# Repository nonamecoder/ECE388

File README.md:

# ECE388
GitHub repository for ECE388 project. Place all project files here.

## Project Description
RFID Automated boom barrier <br/>
### Specifications

###### Inputs <br/>
- Raspberry Pi Pico W(Wireless)
- MRFC522 RFID Reader
  - Detects Mifare 1K Classic Cards based on UID
    - UID ( Unique Identifier)

###### Outputs <br/>

- LCD 
  - Indicate either access granted or access denied.
- Buzzer
  - Access granted buzzer sound1
  - Access denied buzzer sound2
  - Master key buzzer sound for demo!
 - Servo
  - Rotate servo if access is granted
  - Do nothing if access is denied.
  
  ###### Next Steps <br/>
  Following can be achieved using IFTTT, guide can be found [here](https://www.tomshardware.com/how-to/connect-raspberry-pi-pico-w-to-twitter-via-ifttt).
  - If access granted
    - Send notification
  - If access denied
    - Send notification

## References <br/>
- [RFID](https://microcontrollerslab.com/raspberry-pi-pico-rfid-rc522-micropython/)

- [Servo](https://microcontrollerslab.com/servo-motor-raspberry-pi-pico-micropython/)

- [LCD](https://www.tomshardware.com/how-to/lcd-display-raspberry-pi-pico)

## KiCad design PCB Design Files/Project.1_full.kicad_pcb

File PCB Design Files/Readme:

The PCB Design files are added to this folder.

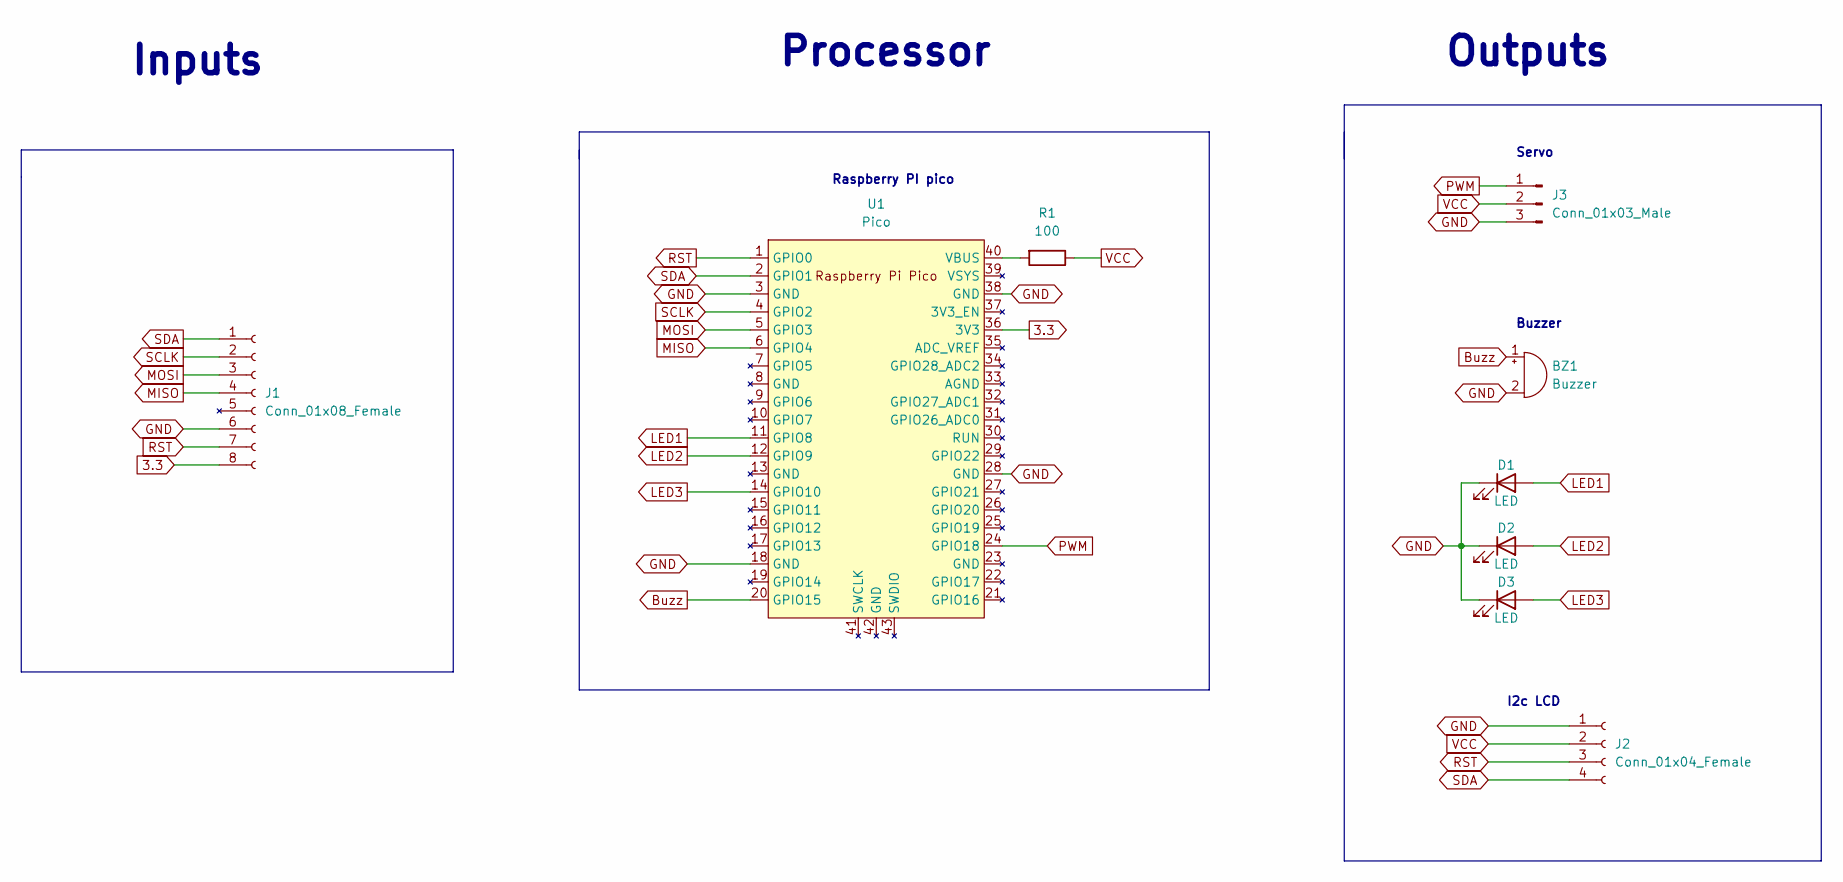
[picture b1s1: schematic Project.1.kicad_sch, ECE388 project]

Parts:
BZ1: Buzzer; Buzzer_12x9.5RM7.6
D1, D2, D3: LED; LED_D5.0mm
J1: Conn_01x08_Female; PinSocket_1x08_P2.54mm_Vertical
J2: Conn_01x04_Female; PinSocket_1x04_P2.54mm_Vertical
J3: Conn_01x03_Male; PinHeader_1x03_P2.54mm_Vertical
R1: 100; R_Axial_DIN0309_L9.0mm_D3.2mm_P12.70mm_Horizontal
U1: Pico; PicoPCB

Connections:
3.3: J1.8 (3.3V), U1.36 (3V3)
Buzz: BZ1.1 (-), U1.20 (GPIO15)
GND: BZ1.2 (+), D1.1 (K), D2.1 (K), D3.1 (K), J1.6 (GND), J2.1 (GND), J3.3, U1.3 (GND), U1.18 (GND), U1.28 (GND), U1.38 (GND)
LED1: D1.2 (A), U1.11 (GPIO8)
LED2: D2.2 (A), U1.12 (GPIO9)
LED3: D3.2 (A), U1.14 (GPIO10)
MISO: J1.4 (MISO), U1.6 (GPIO4)
MOSI: J1.3 (MOSI), U1.5 (GPIO3)
unnamed: R1.2, U1.40 (VBUS)
PWM: J3.1, U1.24 (GPIO18)
RST: J1.7 (RST), J2.3 (SDA), U1.1 (GPIO0)
SCLK: J1.2 (SCK), U1.4 (GPIO2)
SDA: J1.1 (SDA), J2.4 (SCL), U1.2 (GPIO1)
VCC: J2.2 (VCC), J3.2, R1.1

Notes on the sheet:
Buzzer
Processor
Outputs
I2c LCD
Inputs
Servo
Raspberry PI pico

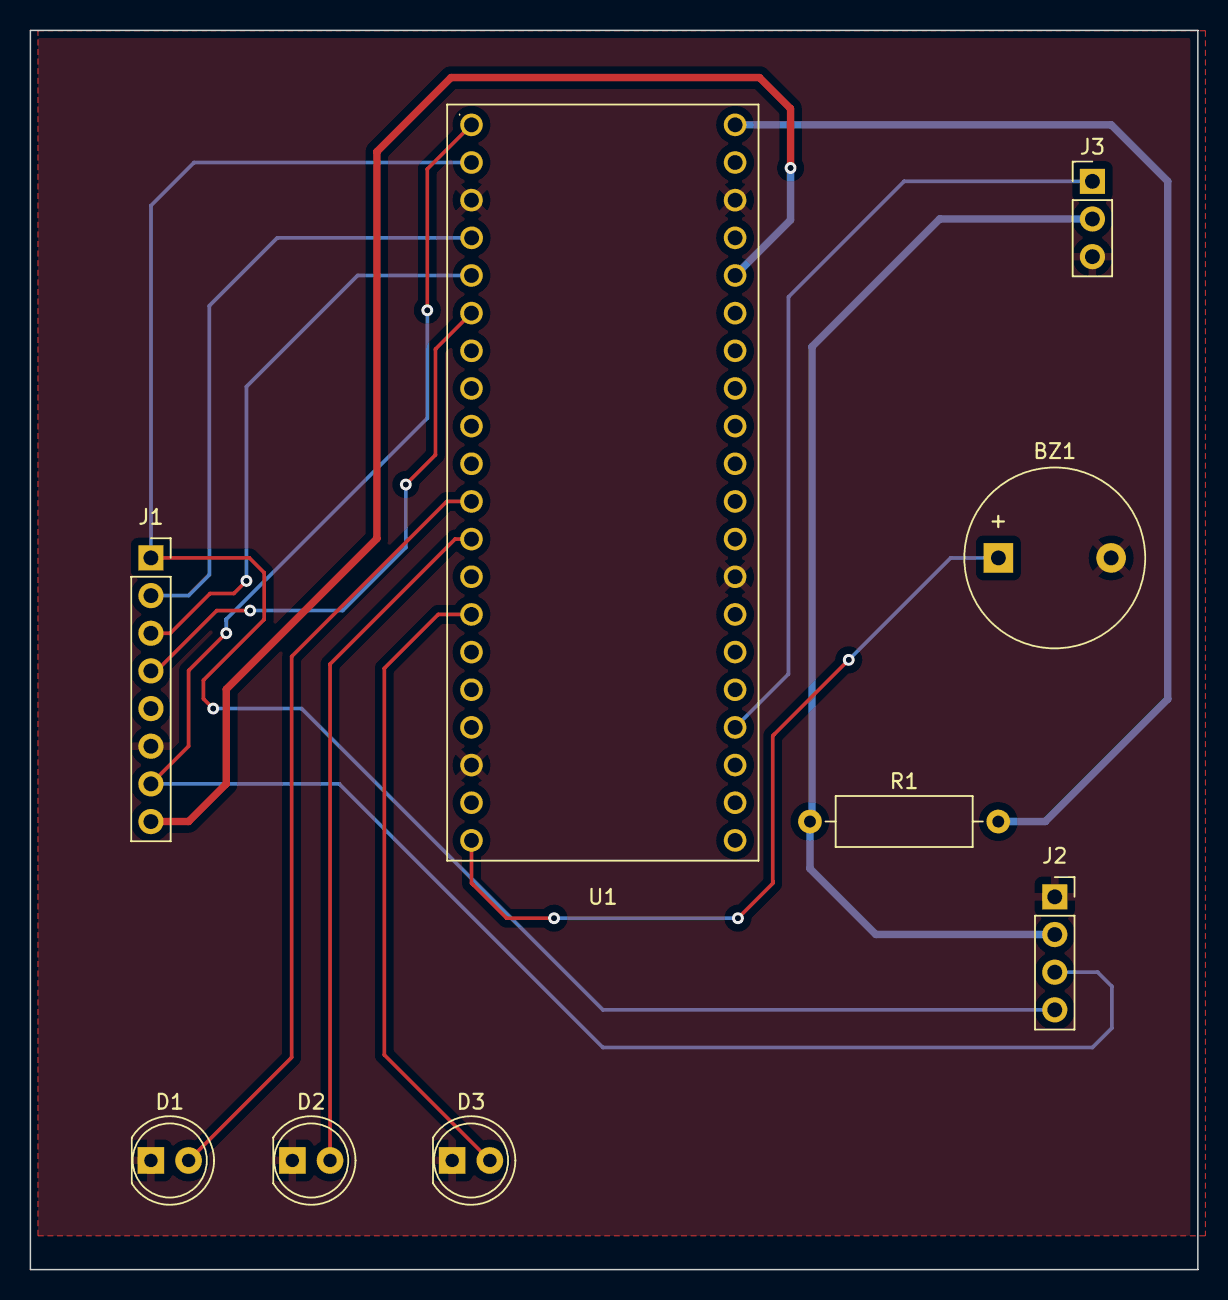
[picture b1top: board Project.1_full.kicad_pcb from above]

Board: 2 copper layers, 78.7 x 83.6 mm, 9 parts (0 on the bottom side), 14 nets.
